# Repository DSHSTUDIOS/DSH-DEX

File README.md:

# DSH-DEX

Dhruv loves Pokémon, so I made him a Poké Ball virtual pet for his birthday back in September. It's small enough to go on his keychain. I'm still putting the first one together, so the pictures below are from CAD. I'll add photos when it's built.

## playing it

Turn it on with the side switch. Slide the red half up to see the OLED and the white half down to get to the buttons. **Feed** gives it a berry, **Pet** makes it happy, and **Select** shows its stats.

If your friend has one too, point the two units at each other and tap **Battle** on both. You get three seconds to shake it and power up your attack. Hold **Battle** for solo practice. Flip the switch off to charge over USB-C.

## pics

**Case open in Fusion**

**PCB** ([populated board in 3D](assets/renders/DSH-DEX-THT-preview.png))

**Schematic** (click to zoom)

## making one

- **Board** · [KiCad files](hardware/kicad/), [Gerbers](hardware/manufacturing/DSH-DEX-Gerbers.zip), [BOM and placement files for the assembler](hardware/manufacturing/Assembly/), and [how to order it](hardware/manufacturing/README.md).
- **Parts** · [BOM with links and prices](hardware/DSH-DEX-BOM.csv). Prices are estimates. I still need a quote for the battery.
- **Case** · [Seven STLs for the print shop](enclosure/Print-Ready/DSH-DEX-Print-STLs.zip). Send them at 100% scale in mm, then [put it together](enclosure/Print-Ready/README.md). The [Fusion and STEP print layouts](enclosure/Print-Ready/) are there too.
- **Firmware** · Pick [Garchomp #0445](firmware/Garchomp/), [Giratina #0487](firmware/Giratina/), or [Metagross #0376](firmware/Metagross/). Use the first-flash file on a blank board and the app file when switching Pokémon so you keep your saves. [Flash instructions](firmware/README.md) · [Arduino code](firmware/dsh_dex/) · [sprites](assets/sprites/)

Run `sh restore-cad.sh` from the repo folder to unpack the assembled Fusion model, PCB STEP, and KiCad 3D models.

# AI USAGE
This section covers how i used ai, so i mainly js used ai for bug fixing (35%~ of code) <--- ik that seems like a lot but im a shitty coder so there was a shit ton of bugs, i also used ai for uploading files since theres no upload limit for ai agents, and i also used it to make the assembly instruction better and more formal from the my current tone it is easier to understand.

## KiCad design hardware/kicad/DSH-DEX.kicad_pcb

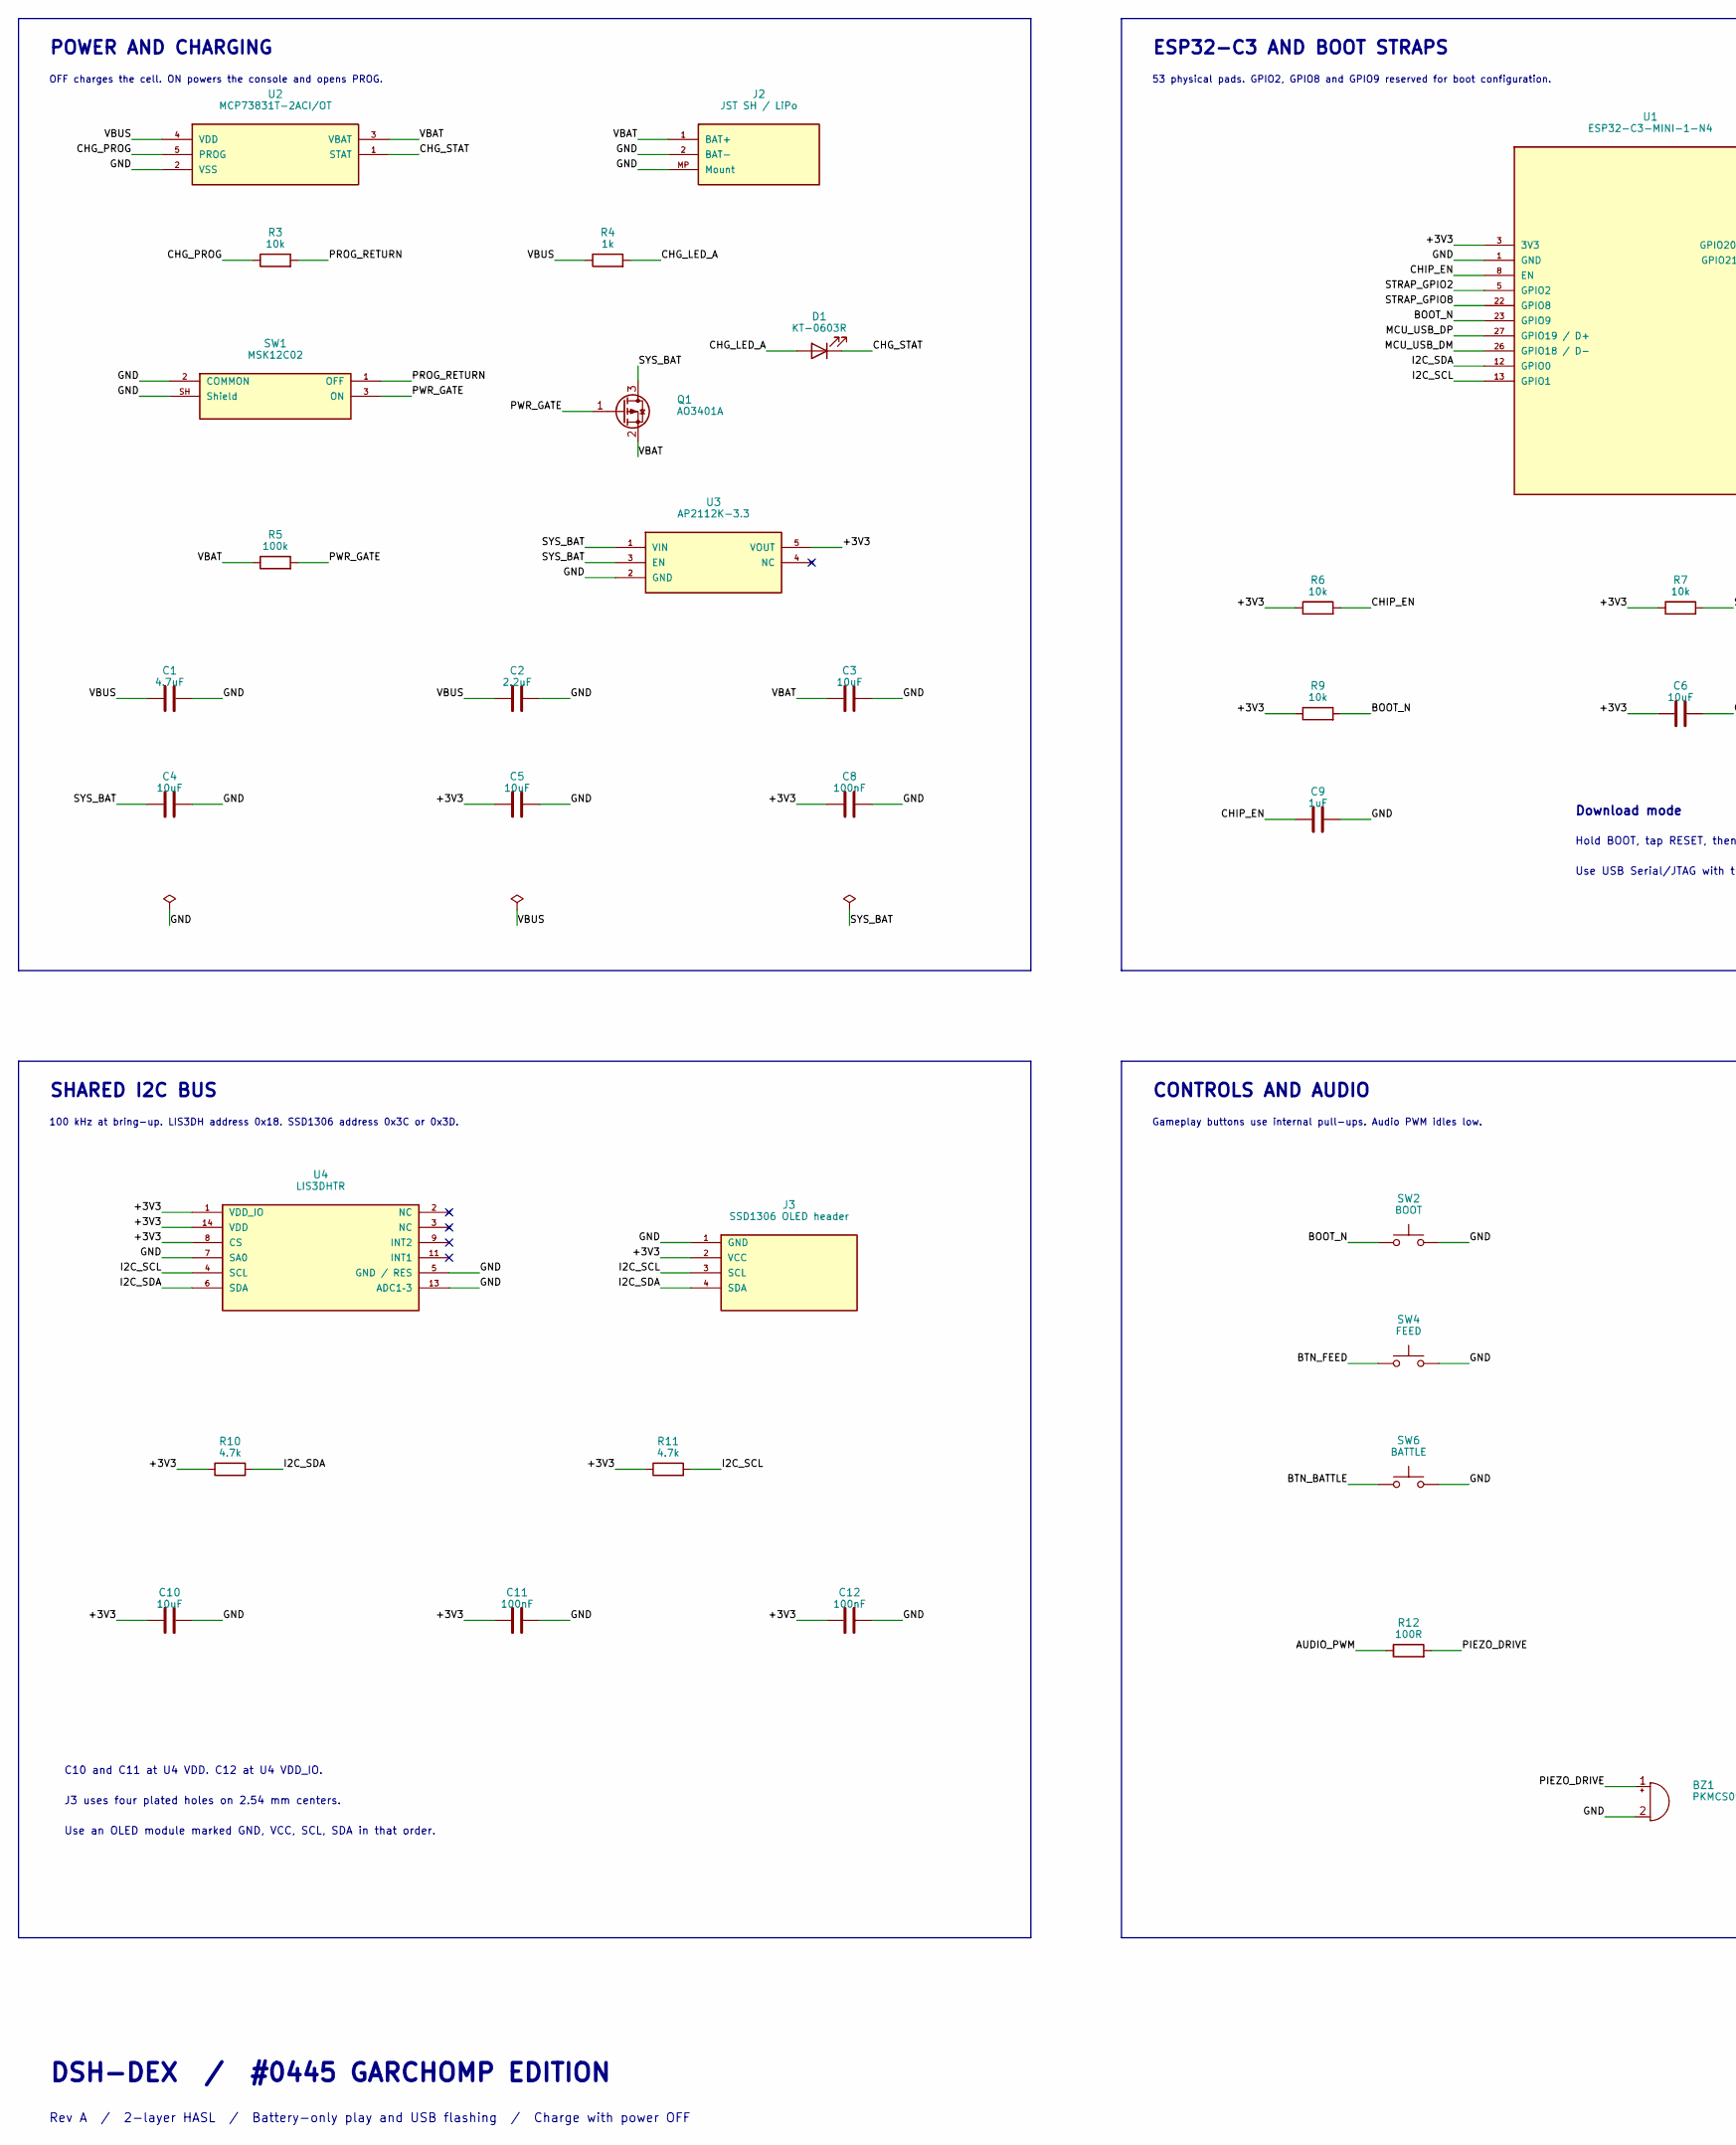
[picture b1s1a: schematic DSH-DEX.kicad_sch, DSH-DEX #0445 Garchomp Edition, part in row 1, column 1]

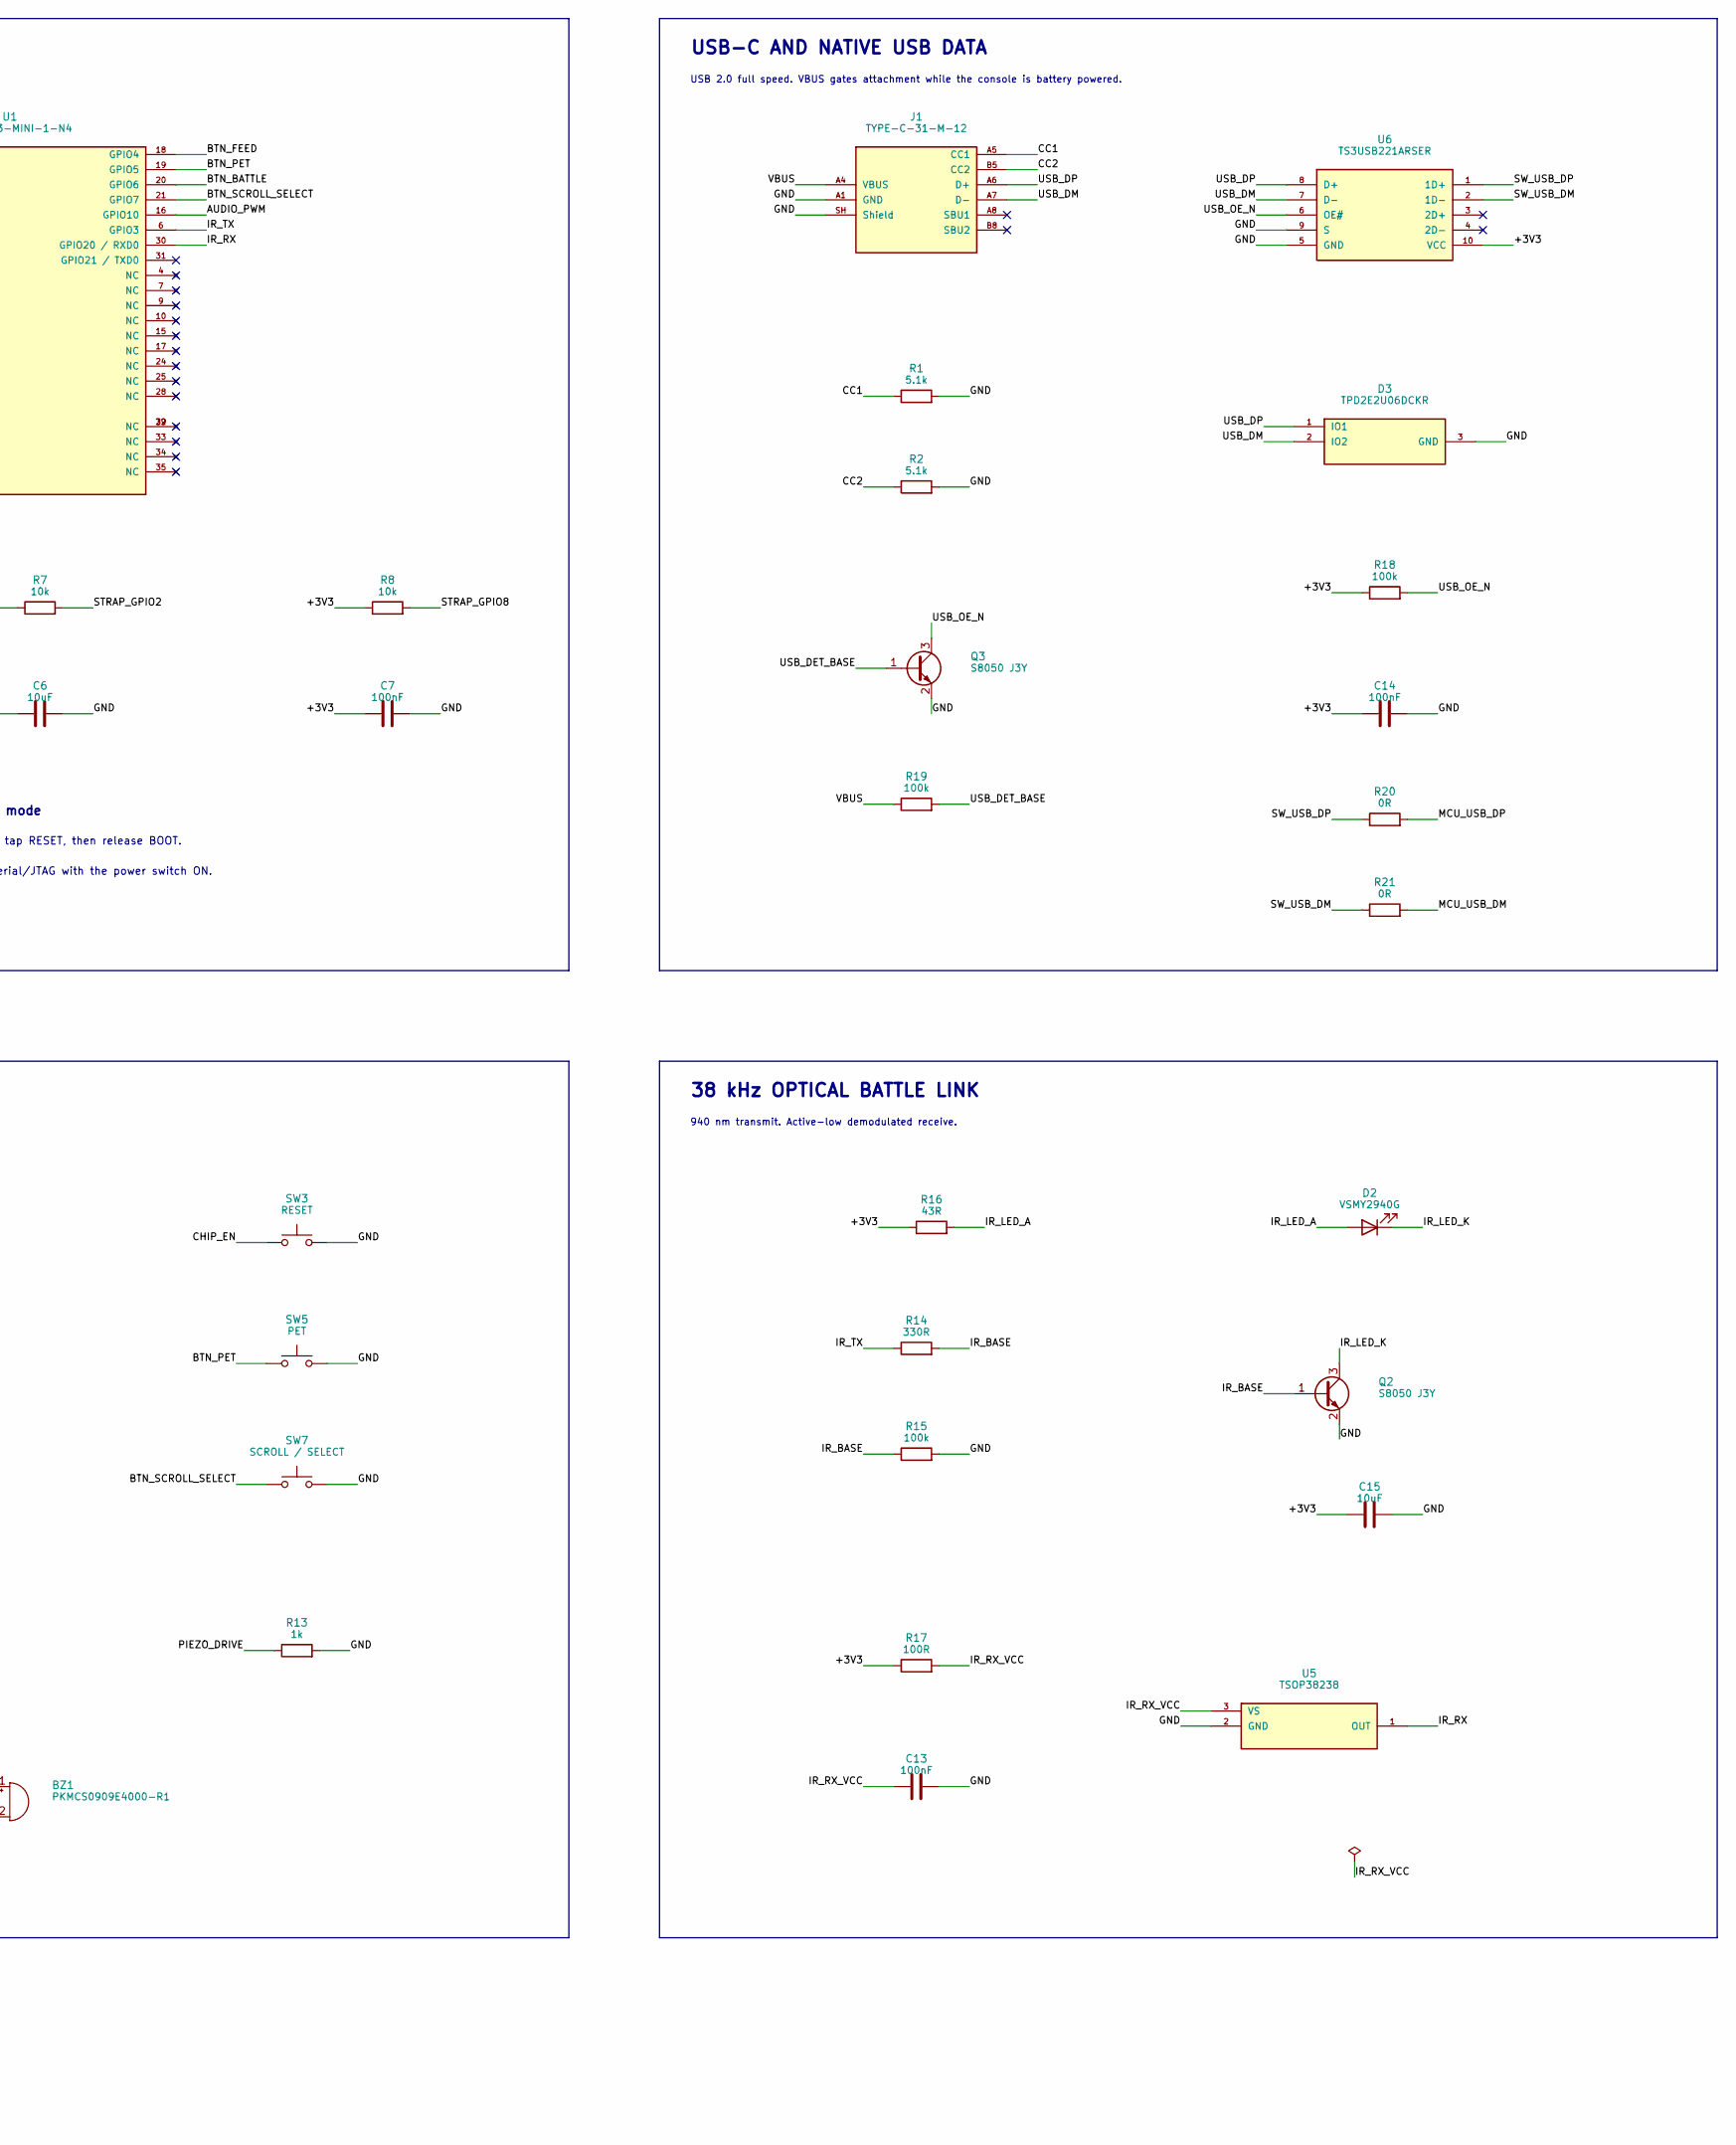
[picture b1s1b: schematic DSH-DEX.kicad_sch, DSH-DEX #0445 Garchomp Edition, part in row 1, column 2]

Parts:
BZ1: PKMCS0909E4000-R1; Buzzer_Murata_PKMCS0909E; MPN PKMCS0909E4000-R1; LCSC Part # C910763
C1: 4.7uF; C_0805_2012Metric; MPN CL21A475KAQNNNE; LCSC Part # C1779
C2: 2.2uF; C_0805_2012Metric; MPN CL21B225KAFNNNE; LCSC Part # C19110
C3, C4, C5, C6, C10, C15: 10uF; C_0805_2012Metric; MPN CL21A106KAYNNNE; LCSC Part # C15850
C7, C8, C11, C12, C13, C14: 100nF; C_0603_1608Metric; MPN CC0603KRX7R9BB104; LCSC Part # C14663
C9: 1uF; C_0603_1608Metric; MPN CL10A105KB8NNNC; LCSC Part # C15849
D1: KT-0603R; LED_0603_1608Metric; MPN KT-0603R; LCSC Part # C2286
D2: VSMY2940G; Vishay_VSMY2940G; MPN VSMY2940G; LCSC Part # C499547
D3: TPD2E2U06DCKR; SOT-323_SC-70; MPN TPD2E2U06DCKR; LCSC Part # C1855726
J1: TYPE-C-31-M-12; USB_C_HRO_TYPE-C-31-M-12_Edge; MPN TYPE-C-31-M-12; LCSC Part # C165948
J2: JST SH / LiPo; JST_SH_BM02B-SRSS-TB_1x02-1MP_P1.00mm_Vertical; MPN BM02B-SRSS-TB(LF)(SN); LCSC Part # C160388
J3: SSD1306 OLED header; OLED_ThroughHole_1x04_P2.54
Q1: AO3401A; SOT-23; MPN AO3401A; LCSC Part # C15127
Q2, Q3: S8050 J3Y; SOT-23; MPN S8050 J3Y; LCSC Part # C2146
R1, R2: 5.1k; R_0603_1608Metric; MPN 0603WAF5101T5E; LCSC Part # C23186
R3, R6, R7, R8, R9: 10k; R_0603_1608Metric; MPN 0603WAF1002T5E; LCSC Part # C25804
R4, R13: 1k; R_0603_1608Metric; MPN 0603WAF1001T5E; LCSC Part # C21190
R5, R15, R18, R19: 100k; R_0603_1608Metric; MPN 0603WAF1003T5E; LCSC Part # C25803
R10, R11: 4.7k; R_0603_1608Metric; MPN 0603WAF4701T5E; LCSC Part # C23162
R12, R17: 100R; R_0603_1608Metric; MPN 0603WAF1000T5E; LCSC Part # C22775
R14: 330R; R_0603_1608Metric; MPN 0603WAF3300T5E; LCSC Part # C23138
R16: 43R; R_0805_2012Metric; MPN 0805W8F430JT5E; LCSC Part # C4368
R20, R21: 0R; R_0603_1608Metric; MPN 0603WAF0000T5E; LCSC Part # C21189
SW1: MSK12C02; SW_SPDT_Shouhan_MSK12C02; MPN MSK12C02; LCSC Part # C431540
SW2: BOOT; SW_SPST_TS-1088-xR020; MPN TS-1088-AR02016; LCSC Part # C720477
SW3: RESET; SW_SPST_TS-1088-xR020; MPN TS-1088-AR02016; LCSC Part # C720477
SW4: FEED; SW_SPST_TS-1088-xR020; MPN TS-1088-AR02016; LCSC Part # C720477
SW5: PET; SW_SPST_TS-1088-xR020; MPN TS-1088-AR02016; LCSC Part # C720477
SW6: BATTLE; SW_SPST_TS-1088-xR020; MPN TS-1088-AR02016; LCSC Part # C720477
SW7: SCROLL / SELECT; SW_SPST_TS-1088-xR020; MPN TS-1088-AR02016; LCSC Part # C720477
U1: ESP32-C3-MINI-1-N4; ESP32-C3-MINI-1; MPN ESP32-C3-MINI-1-N4; LCSC Part # C2838502
U2: MCP73831T-2ACI/OT; SOT-23-5; MPN MCP73831T-2ACI/OT; LCSC Part # C424093
U3: AP2112K-3.3; SOT-23-5; MPN AP2112K-3.3TRG1; LCSC Part # C51118
U4: LIS3DHTR; LGA-16_3x3mm_P0.5mm_LayoutBorder3x5y; MPN LIS3DHTR; LCSC Part # C15134
U5: TSOP38238; Vishay_MINICAST-3Pin; MPN TSOP38238; LCSC Part # C141632
U6: TS3USB221ARSER; Texas_UQFN-10_1.5x2mm_P0.5mm; MPN TS3USB221ARSER; LCSC Part # C128396

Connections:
/+3V3: C5.1, C6.1, C7.1, C8.1, C10.1, C11.1, C12.1, C14.1, C15.1, J3.2 (VCC), R6.1, R7.1, R8.1, R9.1, R10.1, R11.1, R16.1, R17.1, R18.1, U1.3 (3V3), U3.5 (VOUT), U4.1 (VDD_IO), U4.8 (CS), U4.14 (VDD), U6.10 (VCC)
/AUDIO_PWM: R12.1, U1.16 (GPIO10)
/BOOT_N: R9.2, SW2.1, U1.23 (GPIO9)
/BTN_BATTLE: SW6.1, U1.20 (GPIO6)
/BTN_FEED: SW4.1, U1.18 (GPIO4)
/BTN_PET: SW5.1, U1.19 (GPIO5)
/BTN_SCROLL_SELECT: SW7.1, U1.21 (GPIO7)
/CC1: J1.A5 (CC1), R1.1
/CC2: J1.B5 (CC2), R2.1
/CHG_LED_A: D1.2 (A), R4.2
/CHG_PROG: R3.1, U2.5 (PROG)
/CHG_STAT: D1.1 (K), U2.1 (STAT)
/CHIP_EN: C9.1, R6.2, SW3.1, U1.8 (EN)
/GND: BZ1.2 (-), C1.2, C2.2, C3.2, C4.2, C5.2, C6.2, C7.2, C8.2, C9.2, C10.2, C11.2, C12.2, C13.2, C14.2, C15.2, D3.3 (GND), J1.A1 (GND), J1.A12, J1.B1, J1.B12, J1.SH (Shield), J2.2 (BAT-), J2.MP (Mount), J3.1 (GND), Q2.2 (E), Q3.2 (E), R1.2, R2.2, R13.2, R15.2, SW1.2 (COMMON), SW1.SH (Shield), SW2.2, SW3.2, SW4.2, SW5.2, SW6.2, SW7.2, U1.1 (GND), U1.2, U1.11, U1.14, U1.36, U1.37, U1.38, U1.39, U1.40, U1.41, U1.42, U1.43, U1.44, U1.45, U1.46, U1.47, U1.48, U1.49, U1.50, U1.51, U1.52, U1.53, U2.2 (VSS), U3.2 (GND), U4.5 (GND_/_RES), U4.7 (SA0), U4.10, U4.12, U4.13 (ADC1–3), U4.15, U4.16, U5.2 (GND), U6.5 (GND), U6.9 (S)
/I2C_SCL: J3.3 (SCL), R11.2, U1.13 (GPIO1), U4.4 (SCL)
/I2C_SDA: J3.4 (SDA), R10.2, U1.12 (GPIO0), U4.6 (SDA)
/IR_BASE: Q2.1 (B), R14.2, R15.1
/IR_LED_A: D2.2 (A), R16.2
/IR_LED_K: D2.1 (K), Q2.3 (C)
/IR_RX: U1.30 (GPIO20_/_RXD0), U5.1 (OUT)
/IR_RX_VCC: C13.1, R17.2, U5.3 (VS)
/IR_TX: R14.1, U1.6 (GPIO3)
/MCU_USB_DM: R21.2, U1.26 (GPIO18_/_D-)
/MCU_USB_DP: R20.2, U1.27 (GPIO19_/_D+)
/PIEZO_DRIVE: BZ1.1 (+), R12.2, R13.1
/PROG_RETURN: R3.2, SW1.1 (OFF)
/PWR_GATE: Q1.1 (G), R5.2, SW1.3 (ON)
/STRAP_GPIO2: R7.2, U1.5 (GPIO2)
/STRAP_GPIO8: R8.2, U1.22 (GPIO8)
/SW_USB_DM: R21.1, U6.2 (1D-)
/SW_USB_DP: R20.1, U6.1 (1D+)
/SYS_BAT: C4.1, Q1.3 (D), U3.1 (VIN), U3.3 (EN)
/USB_DET_BASE: Q3.1 (B), R19.2
/USB_DM: D3.2 (IO2), J1.A7 (D-), J1.B7, U6.7 (D-)
/USB_DP: D3.1 (IO1), J1.A6 (D+), J1.B6, U6.8 (D+)
/USB_OE_N: Q3.3 (C), R18.2, U6.6 (OE#)
/VBAT: C3.1, J2.1 (BAT+), Q1.2 (S), R5.1, U2.3 (VBAT)
/VBUS: C1.1, C2.1, J1.A4 (VBUS), J1.A9, J1.B4, J1.B9, R4.1, R19.1, U2.4 (VDD)

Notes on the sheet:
POWER AND CHARGING
OFF charges the cell. ON powers the console and opens PROG.
ESP32-C3 AND BOOT STRAPS
53 physical pads. GPIO2, GPIO8 and GPIO9 reserved for boot configuration.
Download mode
Hold BOOT, tap RESET, then release BOOT.
Use USB Serial/JTAG with the power switch ON.
USB-C AND NATIVE USB DATA
USB 2.0 full speed. VBUS gates attachment while the console is battery powered.
SHARED I2C BUS
100 kHz at bring-up. LIS3DH address 0x18. SSD1306 address 0x3C or 0x3D.
C10 and C11 at U4 VDD. C12 at U4 VDD_IO.
J3 uses four plated holes on 2.54 mm centers.
Use an OLED module marked GND, VCC, SCL, SDA in that order.
CONTROLS AND AUDIO
Gameplay buttons use internal pull-ups. Audio PWM idles low.
38 kHz OPTICAL BATTLE LINK
940 nm transmit. Active-low demodulated receive.
DSH-DEX / #0445 GARCHOMP EDITION
Rev A / 2-layer HASL / Battery-only play and USB flashing / Charge with power OFF

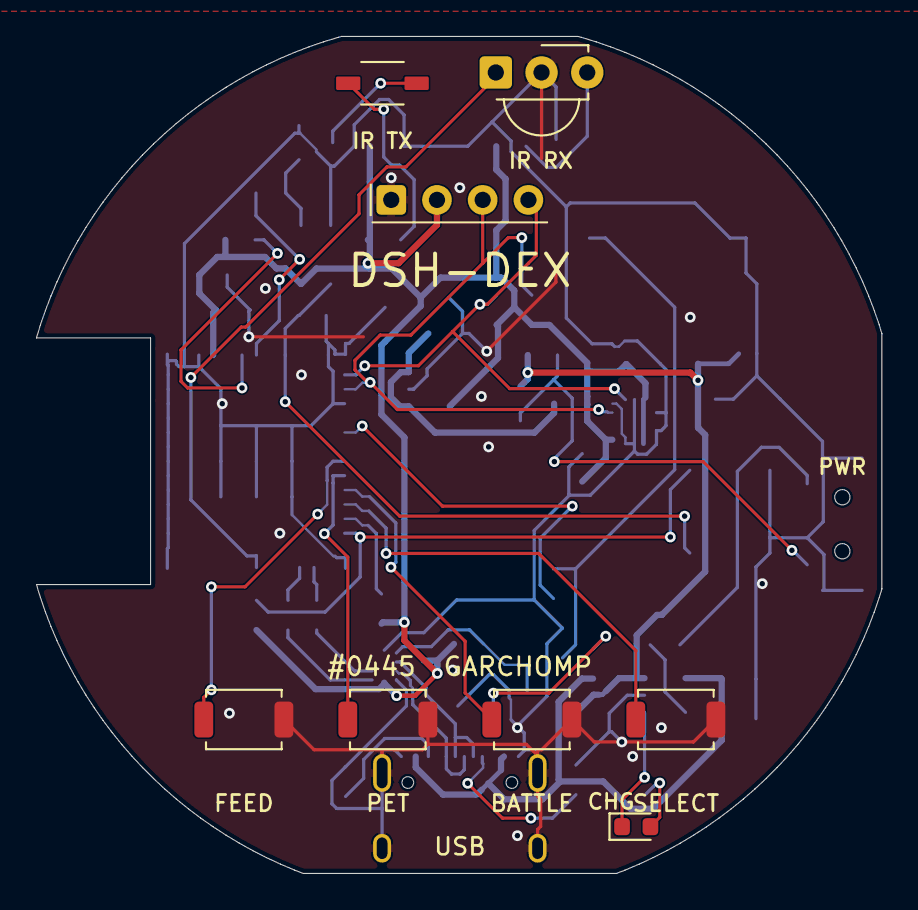
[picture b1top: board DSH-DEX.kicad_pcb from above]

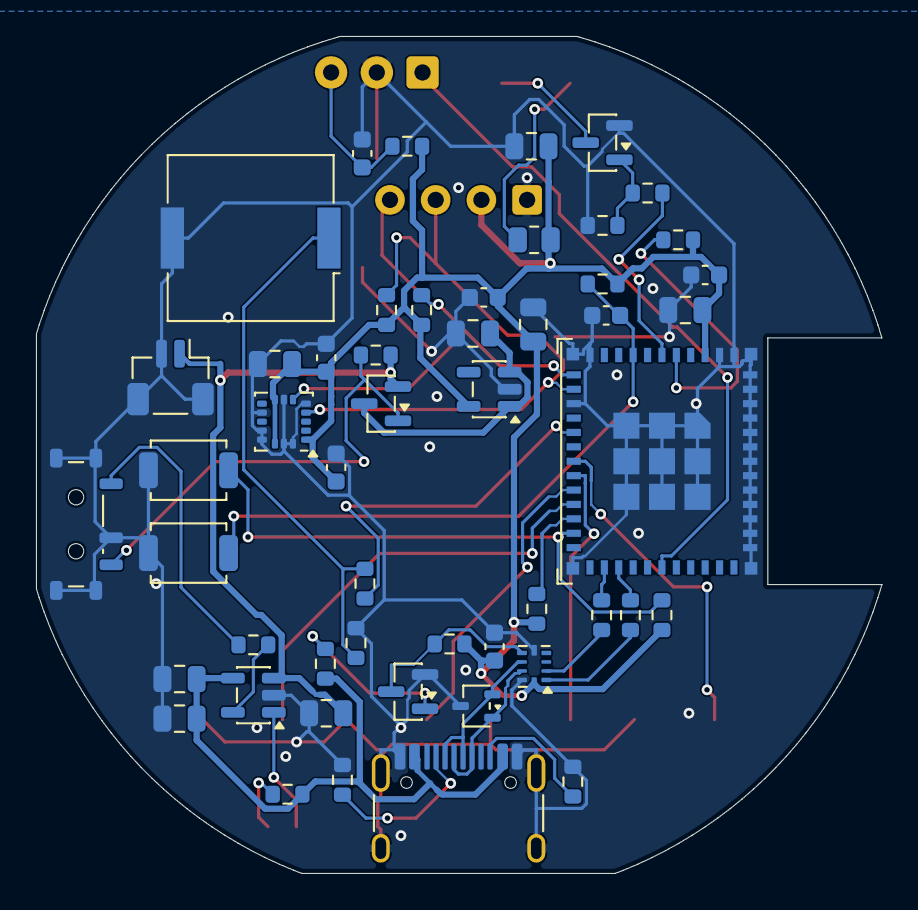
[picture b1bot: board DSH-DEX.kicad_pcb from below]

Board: 2 copper layers, 47.0 x 46.5 mm, 59 parts (51 on the bottom side), 38 nets.

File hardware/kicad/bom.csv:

Designator,Quantity,Value,Manufacturer,MPN,Footprint,LCSC Part #,Assembly
U1,1,ESP32-C3-MINI-1 4 MB PCB antenna,Espressif,ESP32-C3-MINI-1-N4,Custom Espressif MINI-1 53-pad land pattern,C2838502,Check JLCPCB tier and stock
U2,1,4.20 V LiPo charger,Microchip,MCP73831T-2ACI/OT,SOT-23-5,C424093,Check JLCPCB tier and stock
U3,1,3.3 V 600 mA LDO,Diodes Inc.,AP2112K-3.3TRG1,SOT-23-5,C51118,JLCPCB Extended
U4,1,3-axis accelerometer,STMicroelectronics,LIS3DHTR,LGA-16 3x3 mm 0.5 mm LayoutBorder3x5y,C15134,Check JLCPCB tier and stock
U5,1,38 kHz IR receiver,Vishay,TSOP38238,Vishay MINICAST-3Pin THT,C141632,Hand install
U6,1,USB 2.0 data switch,Texas Instruments,TS3USB221ARSER,Texas UQFN-10 1.5x2 mm 0.5 mm RSE,C128396,Check JLCPCB tier and stock
J1,1,USB-C USB 2.0 receptacle,Korean Hroparts,TYPE-C-31-M-12,USB_C_Receptacle_HRO_TYPE-C-31-M-12,C165948,Check JLCPCB tier and stock
J2,1,2-pin 1.00 mm battery connector,JST,BM02B-SRSS-TB(LF)(SN),JST_SH_BM02B-SRSS-TB_1x02-1MP_P1.00mm_Vertical,C160388,Check JLCPCB tier and stock
J3,1,OLED plated through-hole interface,,,"1x04, 2.54 mm pitch, 0.90 mm drills (1 GND / 2 VCC / 3 SCL / 4 SDA)",,Plated carrier holes
DISP1,1,0.96 in SSD1306 128x64 I2C 3.3 V OLED,,,27 x 28 mm module with 4-pin 2.54 mm header,,Verify GND/VCC/SCL/SDA order. Solder module directly into J3 and trim pin tails.
BT1,1,Protected 1S 4.20 V LiPo 100-150 mAh,,,External pack with verified mating plug and polarity,,Select cell with charge rating >=112 mA and qualified discharge capability
SW1,1,SPDT ON-ON slide power/charge selector,SHOU HAN,MSK12C02,SW_SPDT_Shouhan_MSK12C02 SMD 8x2.8 mm,C431540,Check JLCPCB tier and stock
"SW2,SW3,SW4,SW5,SW6,SW7",6,SPST-NO tactile 2 mm high,XUNPU,TS-1088-AR02016,Vendor SMD land pattern 3.9x3 mm body,C720477,Check JLCPCB tier and stock
Q1,1,P-MOSFET high-side battery switch,AOS,AO3401A,SOT-23 G1 S2 D3,C15127,Check JLCPCB tier and stock
"Q2,Q3",2,S8050 NPN,JSCJ,S8050 J3Y,SOT-23 B1 E2 C3,C2146,Check JLCPCB tier and stock
D1,1,Red charge indicator,Hubei KENTO,KT-0603R,LED_0603_1608Metric,C2286,JLCPCB Basic
D2,1,940 nm top-emitting narrow-angle IR LED,Vishay,VSMY2940G,Custom standard gullwing per Vishay drawing,C499547,Check JLCPCB tier and stock
D3,1,Two-channel USB ESD clamp,Texas Instruments,TPD2E2U06DCKR,SC-70-3 DCK,C1855726,Check JLCPCB tier and stock
BZ1,1,Passive external-drive piezo 4 kHz,Murata,PKMCS0909E4000-R1,Vendor two-pad 9x9 mm SMD,C910763,Check JLCPCB tier and stock
"R1,R2",2,5.1 kOhm 1%,UNI-ROYAL,0603WAF5101T5E,R_0603_1608Metric,C23186,Check JLCPCB tier and stock
"R3,R6,R7,R8,R9",5,10 kOhm 1%,UNI-ROYAL,0603WAF1002T5E,R_0603_1608Metric,C25804,JLCPCB Basic
"R4,R13",2,1 kOhm 1%,UNI-ROYAL,0603WAF1001T5E,R_0603_1608Metric,C21190,JLCPCB Basic
"R5,R15,R18,R19",4,100 kOhm 1%,UNI-ROYAL,0603WAF1003T5E,R_0603_1608Metric,C25803,JLCPCB Basic
"R10,R11",2,4.7 kOhm 1%,UNI-ROYAL,0603WAF4701T5E,R_0603_1608Metric,C23162,JLCPCB Basic
"R12,R17",2,100 Ohm 1%,UNI-ROYAL,0603WAF1000T5E,R_0603_1608Metric,C22775,JLCPCB Basic
R14,1,330 Ohm 1%,UNI-ROYAL,0603WAF3300T5E,R_0603_1608Metric,C23138,Check JLCPCB tier and stock
R16,1,43 Ohm 1% 0.125 W,UNI-ROYAL,0805W8F430JT5E,R_0805_2012Metric,C4368,"Confirm sourcing. Alternate: Yageo RC0805FR-0743R2L (43.2 ohm, 0805, 125 mW, 1%) JLCPCB C483157."
"R20,R21",2,0 Ohm,UNI-ROYAL,0603WAF0000T5E,R_0603_1608Metric,C21189,JLCPCB Basic
C1,1,4.7 uF 25 V X5R,Samsung,CL21A475KAQNNNE,C_0805_2012Metric,C1779,JLCPCB Basic
C2,1,2.2 uF 25 V X7R,Samsung,CL21B225KAFNNNE,C_0805_2012Metric,C19110,Check JLCPCB tier and stock
"C3,C4,C5,C6,C10,C15",6,10 uF 25 V X5R,Samsung,CL21A106KAYNNNE,C_0805_2012Metric,C15850,JLCPCB Basic
"C7,C8,C11,C12,C13,C14",6,100 nF 50 V X7R,Yageo,CC0603KRX7R9BB104,C_0603_1608Metric,C14663,JLCPCB Basic
C9,1,1 uF 50 V X5R,Samsung,CL10A105KB8NNNC,C_0603_1608Metric,C15849,JLCPCB Basic

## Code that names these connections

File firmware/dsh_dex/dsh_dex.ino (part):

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
namespace pins {
// Rev A IPC-D-356 netlist and ESP32-C3-MINI-1 schematic symbol.
constexpr uint8_t sda = 0;       // U1 pad 12, I2C_SDA
constexpr uint8_t scl = 1;       // U1 pad 13, I2C_SCL
constexpr uint8_t feed = 4;      // U1 pad 18, BTN_FEED
constexpr uint8_t pet = 5;       // U1 pad 19, BTN_PET
constexpr uint8_t battle = 6;    // U1 pad 20, BTN_BATTLE
constexpr uint8_t select = 7;    // U1 pad 21, BTN_SCROLL_SELECT
constexpr uint8_t audio = 10;    // U1 pad 16, AUDIO_PWM
constexpr uint8_t irTx = 3;      // U1 pad 6, IR_TX
constexpr uint8_t irRx = 20;     // U1 pad 30, IR_RX
}

constexpr uint32_t debounceMs = 25;
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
